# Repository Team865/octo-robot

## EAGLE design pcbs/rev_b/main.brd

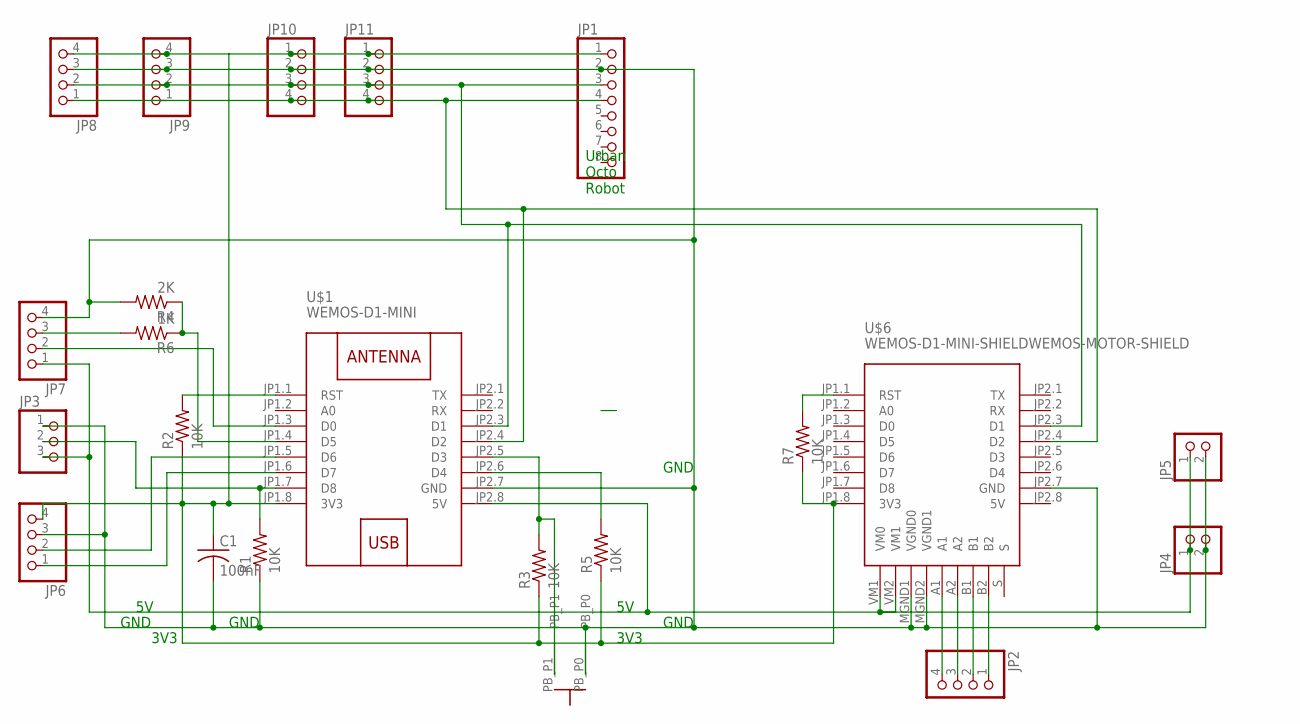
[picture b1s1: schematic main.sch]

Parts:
C1: 100nF; C050-024X044
JP1: PINHD-1X8; 1X08
JP2: PINHD-1X4/90; 1X04/90
JP3: PINHD-1X3; 1X03
JP4, JP5: PINHD-1X2; 1X02
JP6, JP7, JP8, JP9, JP10, JP11: PINHD-1X4; 1X04
R1, R2, R3, R5, R7: 10K; 0204/7
R4: 2K; 0309V
R6: 1K; 0309V
U$1: WEMOS-D1-MINI
U$6: WEMOS-D1-MINI-SHIELDWEMOS-MOTOR-SHIELD; WEMOS-D1-MINI-SHIELD
U$7: BUTTON6X6X10MMSIDE

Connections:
5V: U$6.JP2.8 (5V)
unnamed: JP2.4, U$6.A1
unnamed: R7.2, U$6.JP1.1 (RST)
unnamed: JP3.3, JP4.1, JP5.1, JP7.1, U$1.JP2.8 (5V), U$6.VM1 (VM0), U$6.VM2 (VM1)
unnamed: JP7.3, R6.2
unnamed: JP2.3, U$6.A2
unnamed: JP6.2, U$1.JP1.5 (D6)
unnamed: R5.2, U$1.JP2.6 (D4)
unnamed: R4.1, R6.1, U$1.JP1.4 (D5)
unnamed: R2.2, U$1.JP1.1 (RST)
unnamed: JP3.2, R1.2, U$1.JP1.7 (D8)
unnamed: JP2.2, U$6.B1
unnamed: JP2.1, U$6.B2
unnamed: R3.2, U$1.JP2.5 (D3), U$7.PB_P1
unnamed: JP7.2, U$1.JP1.3 (D0)
unnamed: JP6.1, U$1.JP1.6 (D7)
unnamed: C1.1, JP1.1, JP6.4, JP8.4, JP9.4, JP10.1, JP11.1, R2.1, R3.1, R5.1, R7.1, U$1.JP1.8 (3V3), U$6.JP1.8 (3V3)
unnamed: C1.2, JP1.2, JP3.1, JP4.2, JP5.2, JP6.3, JP7.4, JP8.3, JP9.3, JP10.2, JP11.2, R1.1, R4.2, U$1.JP2.7 (GND), U$6.JP2.7 (GND), U$6.MGND1 (VGND0), U$6.MGND2 (VGND1), U$7.PB_P0
unnamed: JP1.3, JP8.2, JP9.2, JP10.3, JP11.3, U$1.JP2.3 (D1), U$6.JP2.3 (D1)
unnamed: JP1.4, JP8.1, JP9.1, JP10.4, JP11.4, U$1.JP2.4 (D2), U$6.JP2.4 (D2)

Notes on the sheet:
GND
3V3
Urban Octo Robot

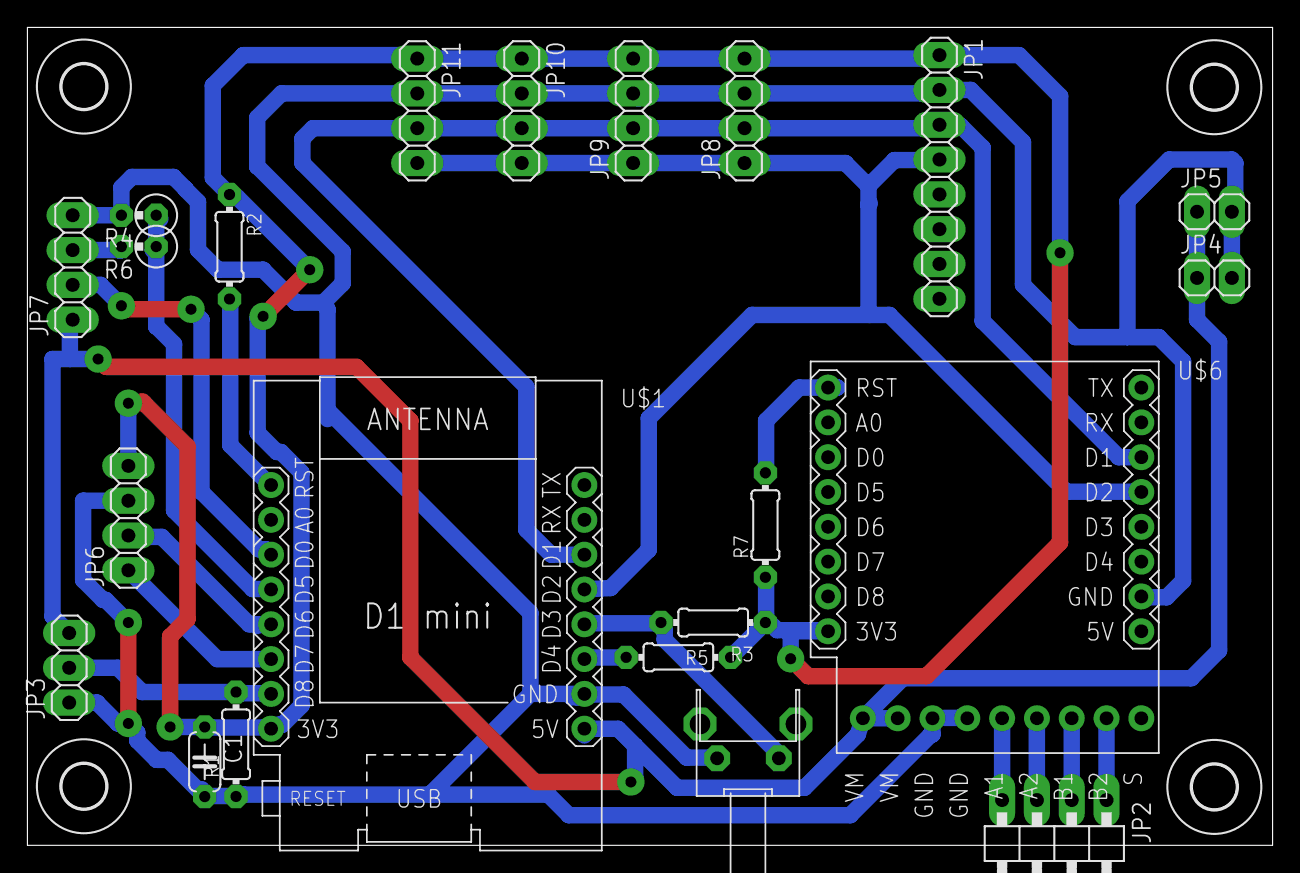
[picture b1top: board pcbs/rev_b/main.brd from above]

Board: 2 copper layers, 90.9 x 59.7 mm, 26 parts (0 on the bottom side), 19 nets.

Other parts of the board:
U$2, U$3, U$4, U$5: 3,2

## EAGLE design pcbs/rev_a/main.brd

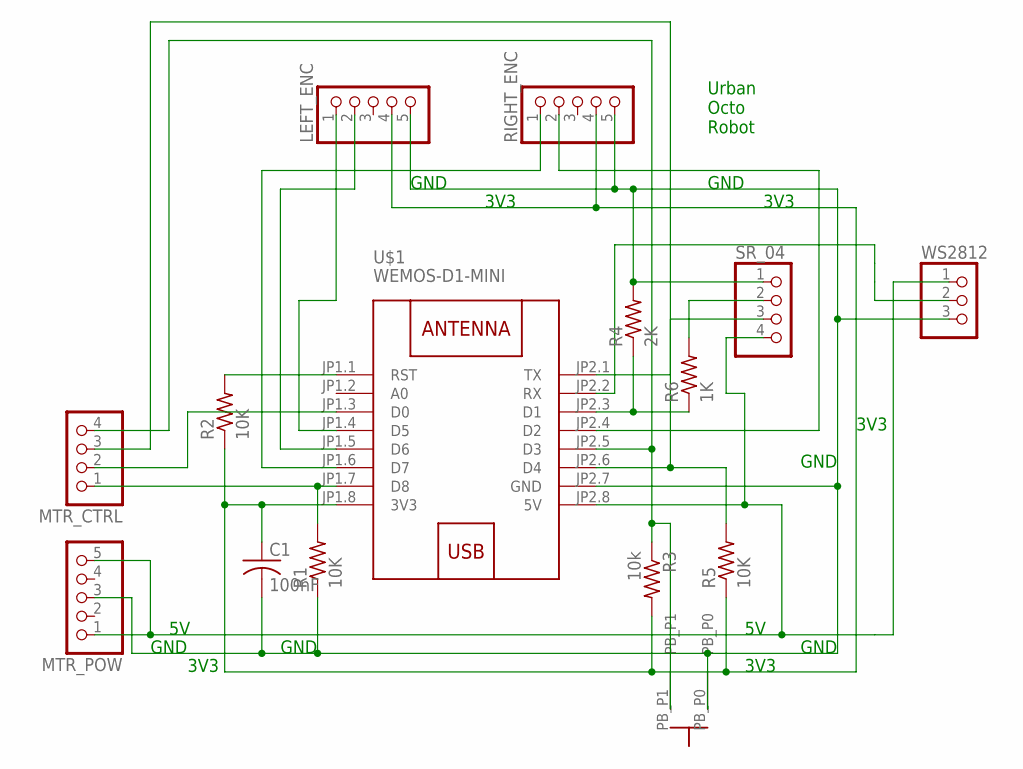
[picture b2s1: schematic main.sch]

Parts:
C1: 100nF; C050-024X044
LEFT_ENC: PINHD-1X5; 1X05
MTR_CTRL: PINHD-1X4; 1X04
MTR_POW: PINHD-1X5/90; 1X05/90
R1, R2, R5: 10K; 0204/7
R3: 10k; 0207/2V
R4: 2K; 0309V
R6: 1K; 0309V
RIGHT_ENC: PINHD-1X5; 1X05
SR_04: PINHD-1X4; 1X04
U$1: WEMOS-D1-MINI
U$7: BUTTON6X6X10MMSIDE
WS2812: PINHD-1X3; 1X03

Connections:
unnamed: U$1.JP2.2 (RX), WS2812.2
unnamed: MTR_POW.1, MTR_POW.5, SR_04.4, U$1.JP2.8 (5V), WS2812.1
unnamed: LEFT_ENC.1, U$1.JP1.4 (D5)
unnamed: MTR_CTRL.2, U$1.JP1.3 (D0)
unnamed: RIGHT_ENC.2, U$1.JP2.4 (D2)
unnamed: LEFT_ENC.2, U$1.JP1.5 (D6)
unnamed: RIGHT_ENC.1, U$1.JP1.6 (D7)
unnamed: C1.1, LEFT_ENC.4, R2.1, R3.2, R5.1, RIGHT_ENC.4, U$1.JP1.8 (3V3)
unnamed: R6.2, SR_04.2
unnamed: MTR_CTRL.4, R3.1, U$1.JP2.5 (D3), U$7.PB_P1
unnamed: R4.1, R6.1, U$1.JP2.3 (D1)
unnamed: SR_04.3, U$1.JP2.1 (TX)
unnamed: MTR_CTRL.3, R5.2, U$1.JP2.6 (D4)
unnamed: R2.2, U$1.JP1.1 (RST)
unnamed: MTR_CTRL.1, R1.2, U$1.JP1.7 (D8)
unnamed: C1.2, LEFT_ENC.5, MTR_POW.3, R1.1, R4.2, RIGHT_ENC.5, SR_04.1, U$1.JP2.7 (GND), U$7.PB_P0, WS2812.3

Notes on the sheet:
GND
3V3
Urban Octo Robot

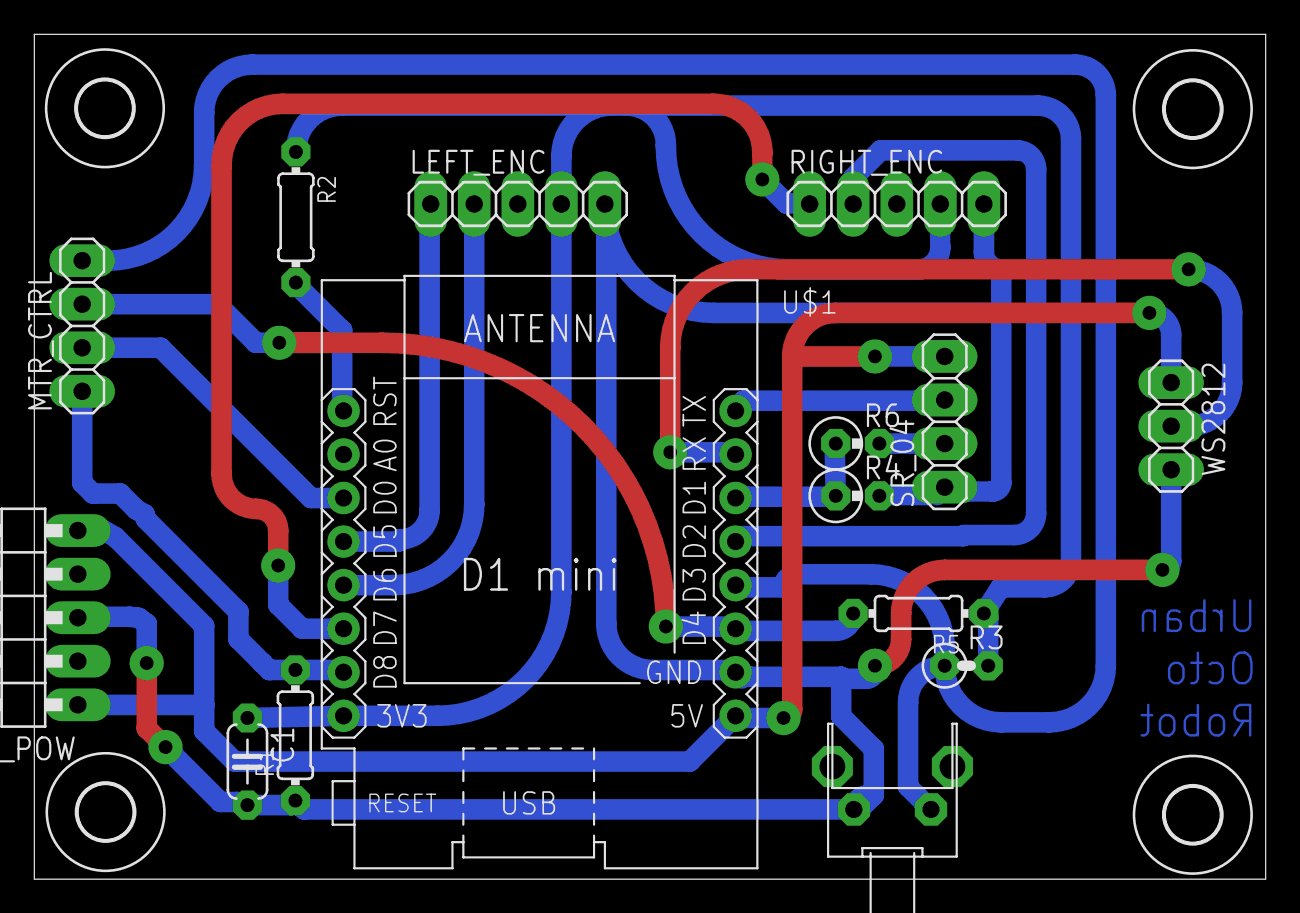
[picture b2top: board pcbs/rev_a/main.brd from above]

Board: 2 copper layers, 71.8 x 49.3 mm, 19 parts (0 on the bottom side), 16 nets.

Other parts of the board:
U$2, U$3, U$4, U$5: 3,2

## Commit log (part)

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2020-06-06 Initial commit (previous project used as a starting point)
2020-06-06 Initial modifications. Set up a command wrangler to parse and send commands to devices.
2020-06-06 Fix ESP8266 specific code.
2020-06-06 Motor controller now works for a single motor
2020-06-07 Add basic presentation with the design intent.
2020-06-07 revisions for readability
2020-06-07 Save actual presentation file
2020-06-07 Clean-up. Bring "action" classes into action namespace
2020-06-07 Clean up more unused code
2020-06-07 do not set hardware state if the state hasn't changed. Makes the simulator more useful.
2020-06-07 More unused code removed.
2020-06-07 fix compile bugs caused by file removal
2020-06-07 rename command wrangler for consistency
2020-06-07 Time namespace work. Introduce concept of type safe number types
2020-06-07 Switch the time since 1970 interface into a typesafe into
2020-06-07 Change action update from loop to periodic. I believe periodic is what First uses in their library Have new periodic return a micro-second time type.
2020-06-07 Code readability changes. Also make the index into the action slot array more typesafe.
2020-06-08 Make interfaces look more like First Robotics interfaces.
2020-06-08 Rename files - more interface alignment
2020-06-08 Documentation pass
2020-06-08 More documentation
2020-06-08 Slight restructure of safe int template
2020-06-08 Proof of concept typesafe int conversion constructors
2020-06-13 Add encoder command
2020-06-13 Speed up esp8266 be caching abstract -> real ID maps into an array
2020-06-13 Begin adding the concept of a high speed timer
2020-06-13 clean-up. Move most time types into time_types.h
2020-06-14 Add a us timer based on the ESP8266's CPU count timer.
2020-06-15 Add a simple mechanism for profiling.
2020-06-15 Have profile gather data from the high speed timer
2020-06-15 Create a reset command for the profiler
2020-06-20 Tweets to the profiling code
2020-06-20 update test
2020-06-20 Create a fairly fast pipe abstract data type and add tests
2020-06-20 New network interface works in simulation mode
2020-06-20 Have command parser accpet a connection instead of an "interface"
2020-06-20 ESP8266 wifi service works with the redone interface. The tail latency on the command that moves data to and from the net is not fantasitic.
    ProcessInput 50% = 11uS 90% = 27uS 98% = 43uS max = 399uS
    L298 Motor Control 50% = 9uS 90% = 10uS 98% = 16uS max = 37uS
    Encoder 50% = 11uS 90% = 11uS 98% = 11uS max = 137uS
    ConnectWatch 50% = 12uS 90% = 19uS 98% = 23uS max = 50uS
    NetConnection 50% = 31uS 90% = 31uS 98% = 31uS max = 2271uS
    ESP8266 HST 50% = 22uS 90% = 23uS 98% = 23uS max = 26uS
2020-06-21 Get !esp8266 platforms to compile again. Mostly.
2020-07-04 Add a command to send encoder data (and anything else) to the host.
2020-07-04 Switch firmward so the robot creates an access point. Greatly improves latency, which will be helpful for prototyping
2020-07-05 Interface for the second motor, "motor b", on GPIO 2 & 0
2020-07-06 Add second encoder
2020-07-12 Added solidworks file for robot skeliton.
2020-07-15 Updated robot model.
2020-07-27 - Start of a PCB that will make the cabling on the robot easier - Update firmware with the PCB's pins
2020-08-05 Added start of example code for the robot.
2020-08-06 Added code for connecting to the robot and sending it commands.
2020-08-08 First candidate board
2020-08-10 Updated robot code to use the DifferentialDrive class.
2020-08-12 Begin work on the sonar range finder command
2020-08-12 Removed redundent code and made the class handling the robot connection a singleton.
2020-08-16 Work on PCB and firmware updates for the SR04 range finder - Move PCB pinouts. I wasn't able to use the TX or RX pins as inputs - Add a WS2812 plug. It might be usable with the last port, and it does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
2020-08-16 Created a pipe system to send information to the robot.
2020-08-16 Renamed files and duplicated existing work.
2020-08-18 Move GPIOs so the firmware can (hopefully) use interrupts instead of polling in encoders.
2020-08-18 Commit files sent to jlpcb for PCB fabrication
2020-08-18 Update images to match the boards that are being fabricated
2020-08-18 Added start of code to be used in video tutorial
2020-08-19 Rename encoder commands to "l" and "r" instead of "a" and "b". L = left, R = right
2020-08-19 Create a pipe data structure for timing Input pin events. This will be used, later, by the encoders driver, and probably the SR04 driver.
2020-08-19 Move Pin, PinState, and names out of the hardware interface. Enables moving the core hardware enums into a light weight types file.
2020-08-19 Split hardware_interface.h into... - hardware_interface.h, which contains the actual interface to the hardware - hardware_types.h, a light weight class for pin related enums & names
2020-08-20 Add the 'concept' of an input event pipe to hardware_esp8266. Also did some restructuring.
2020-08-20 Create a utility for merging two streams of input events in chronological order. For the encoders, which have two pins.
2020-08-20 Create a debouncing ipin event filter + tests.
2020-08-20 Change filters to use pointers instead of references. References were too fancy for the Arduino C++ compiler I'm using
2020-08-20 Step to switching the encoders over to a fully interrupt driven pin model. Switch the encoder command over to an event driven model. The hardware state is still effectively polled under the hood, but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
2020-08-20 Added drive subsystem and hooked it up to Teleop Command
2020-08-20 Added basic documentation to the diffrent functions. Added base to create AutonomousCommand.
2020-08-23 Add "interruptable function" macro. The intention is a macro that tells the ESP8266 compiler to put functions into ram so they can be used in interrupt functions. Use more primitive data structures (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
2020-08-24 Encoder and debugging features - Work to help the encoder modules compute rotation speed. - Renaming. Encoder and Motor modules are now left and right. - There is now a motora command that turns both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
2020-08-24 Switch encoders to interrupt driven input Also fix a crash bug in the profiling code.
2020-08-24 Emergency autonomus fix.
2020-08-25 Switch SR04 range finder to use interrupt driven IO infrastructure.
2020-08-25 Add the sonar range finder to the datasend command. datasend=1 will now generate a RNG reading that has the distance of the nearest object in mm Limit datasend to 10 samples / second - the update tim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
2020-08-25 Simplification. Class-wide distance is no longer needed.
2020-08-25 Have the SR04 take the medium of 3 samples.
2020-08-25 Hardware support for WS2812 LED strips
2020-08-25 Hook LEDs up to encoder and sonar range finder. Gives visual feedback on the robot state that may help with debugging.
2020-09-17 Tune range finder LEDs - Ignore invalid sensor requests. The green flashes are visually distracting - Move the "far" from 140cm to 50cm. - Remove magic number.
2020-09-17 Finished fake FIRST encoder class.
2020-09-17 Added finishing touches on the CAD.
2020-09-18 Today's work on the P controler.
2020-09-20 Update to the PI controler.
2020-09-24 Tighten up the encoders - Do debouncing inside the interrupts. The odd encoder is very noisy and overload the event pipe. When that happens the encoder loses its value. - Tighten up the encoder veloc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
2020-09-24 Increase the polling time on the encoders from 10 times / second to 100 times / second. - Should improve the quality of the data being sent back to the host computer a tiny bit.
2020-10-04 Documentation clean-up + start usage documentation.
2020-10-04 Readability refactorings inspired by "Uncle Bob" of clean code fame.
2020-12-14 Add a VC Code workspace to the tutorial program
2020-12-14 Branch from tutorialcode example
2020-12-14 Work on position/ autonomous tutorial code.... - OctoDriveSubsystem.java: Modify to try to compute the current angle and position. Remove PID code. - TurnCommand.java: A simple command to automatical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
2020-12-16 - Fixes to the angle code in OctoDriveSubsystem.java. The math is easier to follow, but the accuracy of the angles seems to be hurt by quantizaion effects on the encoder during tight turns. - TurnCom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
2020-12-22 Autonomous mode demo...
    Robot will semi-accurately hit three way-points.
2020-12-26 Convert robot example code to use First Robotics 2D Math lib pass.
2020-12-26 Change OctoDriveSystem odometry code to return a WPILib standard Rotation2d.
2020-12-26 Documentation & readability pass on the "Move To" command
2020-12-26 Documentaion & renaming pass on the Turn Command.
2020-12-26 Sync phi computation to match paper @ https://ocw.mit.edu/courses/electrical-engineering-and-computer-science/6-186-mobile-autonomous-systems-laboratory-january-iap-2005/study-materials/odomtutorial.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
    Result doesn't seem quite as good, but it's good enough, and the explanation is much easier to follow.
2020-12-26 Align OctoDriveSububsystem odometry to First Robotics standard interface in https://docs.wpilib.org/en/stable/docs/software/kinematics-and-odometry/differential-drive-odometry.html
2020-12-27 Move EncoderPair class out of the Drive Train.
2020-12-27 Move concept of a "change in encoder state" out of the OctoDriveSubsystem class. Also add an interface for getting the drive train's encoder state.
2020-12-27 Documentation.
2020-12-28 Changes driven by review feedback: - Odometry subsystem should be named Subsystem - Separate out the Odometry math from the update. I've made a new class, DifferentialDriveOdometryNoGyro for the math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
2021-06-06 Move firmware sources to firmware_v1. There will soon be a firmware_v2.
2021-06-06 Move top level firmware directories. It makes sense to keep the firmware all in one place, given that most of the delierable is First Robotics demo code (or should be)
2021-06-06 Test and simulator compiles again.
2021-06-06 Branch to v2
2021-06-06 Temp move to create a copy with history.
2021-06-06 Add cmake files to get the v2 firmware simulator working.
2021-06-26 Remove pins from the motor and encoder interface. Will be done using I2C on the second robot. Also remove include directive from the cmakefile. There are now multiple copies of the same file, so incl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
2021-06-27 - Begin adding I2C interface to the hardware abstraction - Switch pins to the rev 2 prototype board - Add rev 2 eagle files.
2021-07-18 Enabled serial debug for version 2.0
2021-07-23 Added a scan for I2C devices durring motor init.
2021-07-24 Removed code unessisary for the new motor controller.
2021-08-01 rev.b board updates - add more I2C busses for expansion - Add 5v power jumpers for expansion - Motor controller is now powered by 5v line from circuit board (less wires)
2021-08-05 Updated hardwear interface to include more functions from the Wire class.
2021-08-05 Added prototype code for talking to the I2C motor controler.
2021-08-05 Removed obsolite code.
2021-08-06 Fixed I2C motor connection.
2021-08-12 GY-521 Gyroscope firmware support.
2021-08-13 Removed unneeded code.
2021-08-24 Added basics of encoder reading.
2021-08-27 Update rev2 circuit board
2021-08-29 Fixed infinite loop bug.
2021-09-03 Continued work on making encoder outputs work.
2021-09-03 Fixed encoder output.
2021-09-04 Updated encoder code to allow for looping encoder stuff.
2021-09-19 Files sent for revb board manufacturing
2021-09-19 Wheels & Tires for the RevB Robot.
2021-10-17 Organised example code.
2021-10-17 Organised example robot code.
2021-10-17 Re-organised everything.
2021-10-30 Modify example Java code to align with 2021 alpha WPILib interface.
2021-10-31 Revert "Modify example Java code to align with 2021 alpha WPILib interface."
    This reverts commit a9d40d9e8608c11dc74ffc835dbebec86b108688.
2021-10-31 Create project - hello world tutorial
2021-10-31 Copy tutorial 1 -> tutorial 2
2021-10-31 copy tutorial 2 -> tutorial 3
2021-10-31 Display the status of Trigger on Smartdashboard
2021-10-31 Copy Tutorial 3 -> Tutorial 4
2021-10-31 Actually copy tutorial 3 -> tutorial 4
2021-10-31 Changes to get the training robot moving

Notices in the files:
parts and their libraries:
diy-modules: Released under the Creative Commons Attribution 4.0 International License: http://creativecommons.org/licenses/by/4.0
